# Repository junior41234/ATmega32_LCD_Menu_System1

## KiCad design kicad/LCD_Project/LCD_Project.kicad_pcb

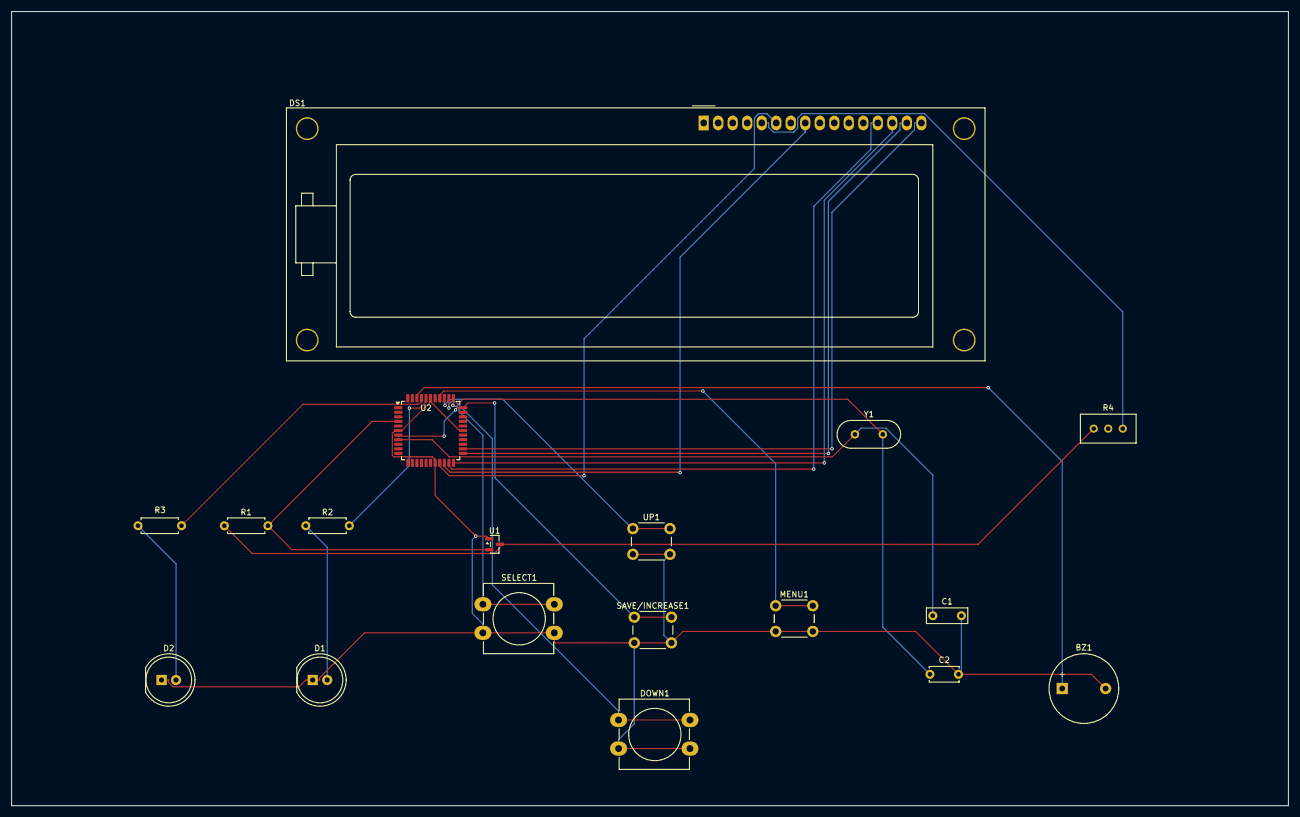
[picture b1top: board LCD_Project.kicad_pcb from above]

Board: 2 copper layers, 223.5 x 139.0 mm, 18 parts (0 on the bottom side), 22 nets.

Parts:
BZ1: Buzzer; Buzzer_12x9.5RM7.6
C1: C; C_Rect_L7.0mm_W2.5mm_P5.00mm
C2: C; C_Disc_D5.0mm_W2.5mm_P5.00mm
D1, D2: LED; LED_D8.0mm
DOWN1: SW_PUSH-12mm_Wuerth-430476085716
DS1: HY1602E
MENU1: SW_PUSH_6mm_H5mm
R1, R2, R3: R; R_Axial_DIN0207_L6.3mm_D2.5mm_P7.62mm_Horizontal
R4: Potentiometer; Potentiometer_Bourns_3296W_Vertical
SAVE/INCREASE1: SW_PUSH_6mm_H5mm
SELECT1: SW_PUSH-12mm_Wuerth-430476085716
U1: LM809; SOT-23
U2: ATmega32-16A; TQFP-44_10x10mm_P0.8mm
UP1: SW_PUSH_6mm_H5mm
Y1: Crystal; Crystal_HC49-U_Vertical

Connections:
+5V: R1.1, R4.3, U1.3 (VCC)
GND: BZ1.2 (-), C1.2, C2.2, D1.1 (K), D2.1 (K), DOWN1.2, MENU1.2, SAVE/INCREASE1.2, SELECT1.2, U1.1 (GND), U2.6 (GND), U2.18 (GND), U2.28 (GND), U2.39 (GND), UP1.2
unnamed: BZ1.1 (+), U2.42 (PB2)
unnamed: D1.2 (A), R2.1
unnamed: D2.2 (A), R3.1
unnamed: DS1.13 (DB4), U2.21 (PC2)
unnamed: DS1.14 (DB5), U2.22 (PC3)
unnamed: DS1.15 (DB6), U2.23 (PC4)
unnamed: DS1.16 (DB7), U2.24 (PC5)
unnamed: DS1.8 (E), U2.20 (PC1)
unnamed: DS1.6 (RS), U2.19 (PC0)
unnamed: DS1.5 (Vo), R4.1
unnamed: R1.2, U1.2 (~RESET), U2.4 (~RESET)
unnamed: MENU1.1, U2.37 (PA0)
unnamed: U2.36 (PA1), UP1.1
unnamed: DOWN1.1, U2.35 (PA2)
unnamed: SELECT1.1, U2.34 (PA3)
unnamed: SAVE/INCREASE1.1, U2.33 (PA4)
unnamed: R2.2, U2.40 (PB0)
unnamed: R3.2, U2.41 (PB1)
unnamed: C1.1, U2.8 (XTAL1), Y1.1
unnamed: C2.1, U2.7 (XTAL2), Y1.2

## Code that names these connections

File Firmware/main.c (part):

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// --- LCD PIN DEFINITIONS (PORTC) ---
#define LCD_DIR      DDRC
#define LCD_PORT     PORTC
#define RS           PC0
#define EN           PC1
// LCD D4-D7 lines are mapped to PC2-PC5

// --- BUTTON PIN DEFINITIONS (PORTA) ---
#define BUTTON_PIN   PINA
#define BTN_MENU     PA0
#define BTN_UP       PA1
#define BTN_DOWN     PA2
#define BTN_SELECT   PA3
#define BTN_SAVE     PA4

// --- PERIPHERAL PIN DEFINITIONS (PORTB) ---
#define LED_DIR      DDRB
#define LED_PORT     PORTB
#define LED_STATUS   PB0
#define LED_MODE     PB1
#define BUZZER       PB2

// --- SYSTEM STATE MACHINE ---
typedef enum {
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
// --- LCD DRIVER FUNCTIONS (4-BIT MODE) ---
void lcd_command(unsigned char cmd) {
    // Send High Nibble (D7-D4) shifted to match PC2-PC5
    LCD_PORT = (LCD_PORT & 0x03) | ((cmd & 0xF0) >> 2);
    LCD_PORT &= ~(1 << RS); // RS = 0 for instruction
    LCD_PORT |= (1 << EN);
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    LCD_PORT &= ~(1 << EN);
    _delay_us(200);

    // Send Low Nibble (D3-D0) shifted to match PC2-PC5
    LCD_PORT = (LCD_PORT & 0x03) | ((cmd & 0x0F) << 2);
    LCD_PORT |= (1 << EN);
    _delay_us(1);
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    // Force PORTA to operate strictly as digital pins.
    ADCSRA &= ~(1 << ADEN);

    // Configure LCD control & data pins as outputs (PC0 - PC5)
    LCD_DIR |= 0x3F;

    // Configure Status LED, Mode LED, and Buzzer as outputs (PB0, PB1, PB2)
    LED_DIR |= (1 << LED_STATUS) | (1 << LED_MODE) | (1 << BUZZER);
    LED_PORT &= ~((1 << LED_STATUS) | (1 << LED_MODE) | (1 << BUZZER));

    // Configure Menu/Navigation keys as inputs (PA0 - PA4)
    DDRA &= ~0x1F;
    PORTA |= 0x1F; // Enable internal pull-ups (Active Low buttons)
}
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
